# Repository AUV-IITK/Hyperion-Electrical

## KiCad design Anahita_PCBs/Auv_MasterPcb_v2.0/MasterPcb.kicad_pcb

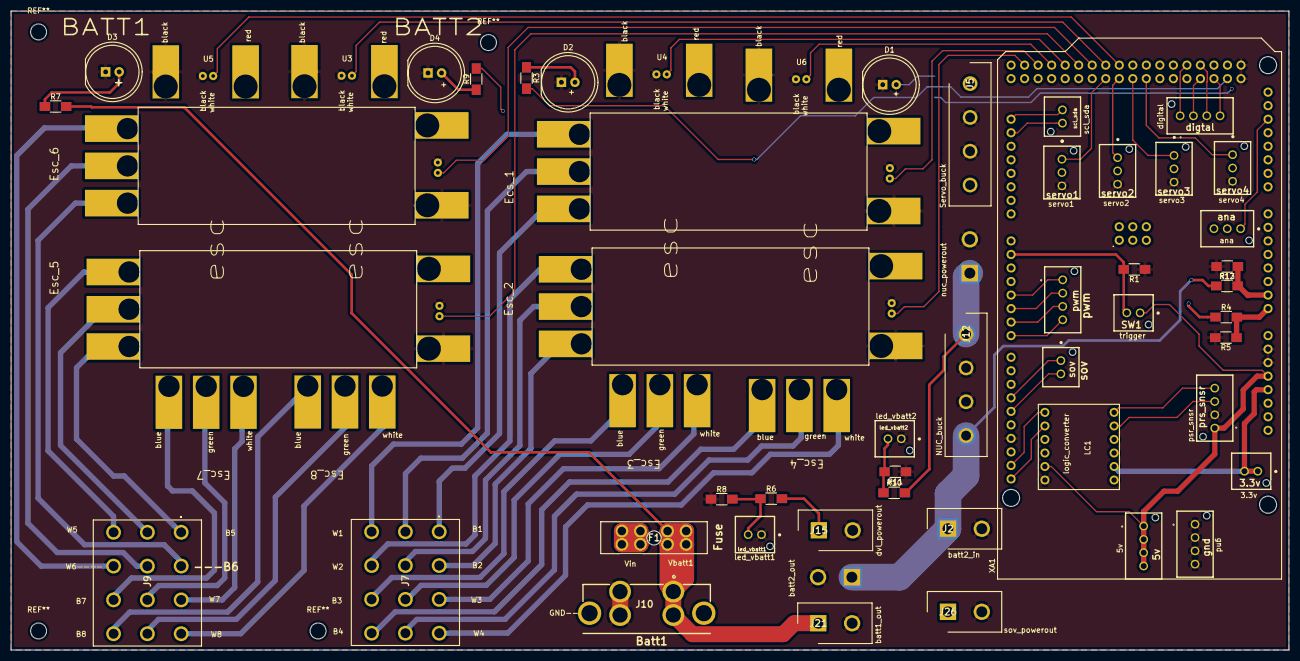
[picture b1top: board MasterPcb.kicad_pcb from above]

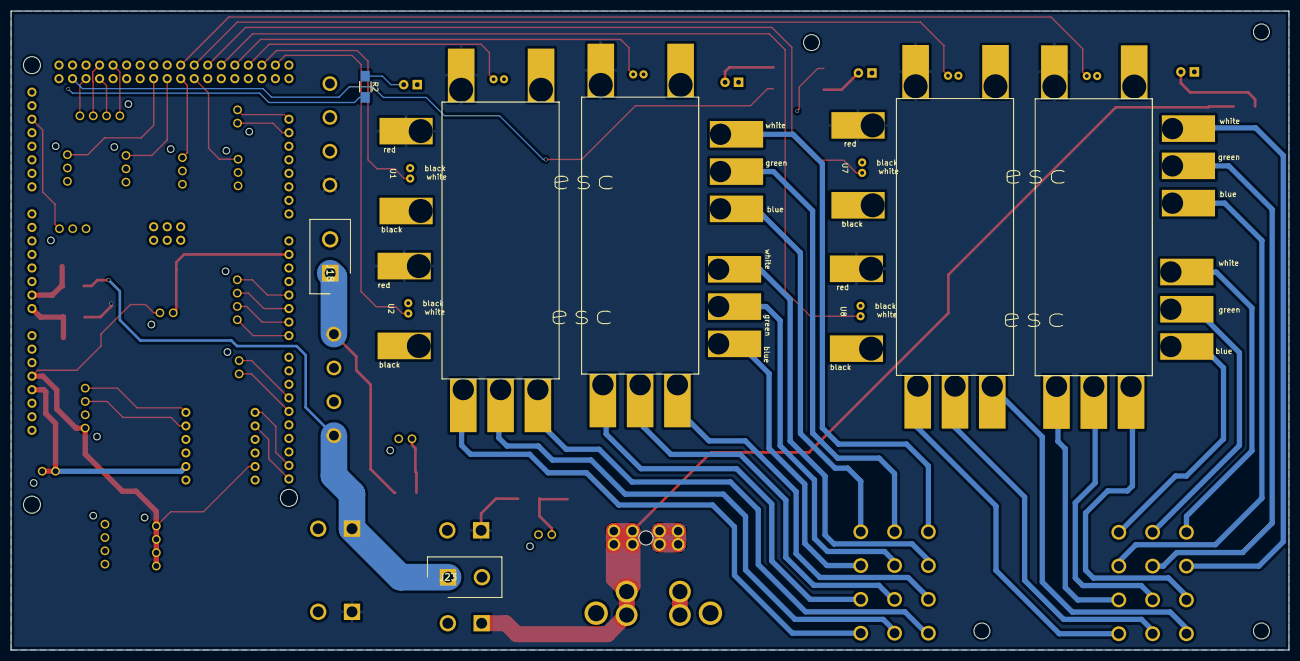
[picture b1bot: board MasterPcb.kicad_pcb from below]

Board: 4 copper layers, 240.0 x 120.0 mm, 55 parts (7 on the bottom side), 74 nets.

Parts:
3.3v: 3.3V_extras; 1x2_mini_lock
5v: 5V_extra; 1x4_mini_lock
D1, D2, D3, D4: LED; LED_D10.0mm
F1: Fuse
J2: nuc_battery; 1x2_Molex
J5: 5V_buck_servo; 1x4_Molex
J7: Thruster_1-4; 4_3connector
J9: Thruster_5-8; 4_3connector
J10: Thruster_power; power
J12: 19V_buck_nuc; 1x4_Molex
J15: dvl_power; 1x2_Molex
J18: Nuc_power; 1x2_Molex
J21: vbatt1_powerout; 1x2_Molex
J23: vbatt2_powerout; 1x2_Molex
J26: Sov_powerout; 1x2_Molex
LC1: Logic_Converter
R1, R2, R3, R5, R7, R9, R13: 1K; R_1206_HandSoldering
R4, R12: 24K; R_1206_HandSoldering
R6, R10: 1k; R_1206_HandSoldering
R8, R11: 4k; R_1206_HandSoldering
SW1: SW_DIP_x01; 1x2_mini_lock
U1, U2, U7, U8: ESCPINS; esc_redefined
U3, U4, U5, U6: ESCPINS; esc_mirror_redefined
XA1: Arduino_Mega2560_Shield
ana: Analog_Extras; 1x3_mini_lock
digtal: Dig_Extras; 1x4_mini_lock
gnd: GND_extras; 1x4_mini_lock
led_vbatt1: Led_vbatt1; 1x2_mini_lock
led_vbatt2: Led_vbatt2; 1x2_mini_lock
prs_snsr: Pressure_sensor_conn; 1x4_mini_lock
pwm: PWM_extras; 1x4_mini_lock
scl_sda: SDA_SCL_extras; 1x2_mini_lock
servo1: servo1; 1x3_mini_lock
servo2: servo2; 1x3_mini_lock
servo3: servo3; 1x3_mini_lock
servo4: servo4; 1x3_mini_lock
sov: Sov; 1x2_mini_lock

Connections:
/3.3V: 3.3v.1, 3.3v.2, LC1.8, XA1.3V3
/5V: 5v.1, 5v.2, 5v.3, 5v.4, LC1.2, SW1.1, XA1.5V1, prs_snsr.1
/5VBC: J5.1, servo1.2, servo2.2, servo3.2, servo4.2
/A0: R4.2, R5.1, XA1.A0
/A1: R12.2, R13.1, XA1.A1
/ANA1: XA1.A13, ana.1
/ANA2: XA1.A14, ana.2
/ANA3: XA1.A15, ana.3
/B1: J7.1, U1.1
/B2: J7.4, U2.1
/B3: J7.9, U4.3
/B4: J7.12, U6.3
/B5: J9.1, U8.1
/B6: J9.4, U7.1
/B7: J9.9, U5.3
/B8: J9.12, U3.3
/DIG1: XA1.D47, digtal.1
/DIG2: XA1.D48, digtal.2
/DIG3: XA1.D49, digtal.3
/DIG4: XA1.D50, digtal.4
/DVL: F1.5, F1.6, F1.7, F1.8, J5.4, J15.1, J26.1, R4.1, R6.2, U1.6, U2.6, U3.7, U4.7, U5.7, U6.7, U7.6, U8.6
/G1: J7.2, U1.2
/G2: J7.5, U2.2
/G3: J7.8, U4.2
/G4: J7.11, U6.2
/G5: J9.2, U8.2
/G6: J9.5, U7.2
/G7: J9.8, U5.2
/G8: J9.11, U3.2
/IN_1: XA1.D11, sov.1
/IN_2: XA1.D12, sov.2
/Led_vbatt1: R6.1, R8.2, led_vbatt1.2
/Led_vbatt2: R10.1, R11.2, led_vbatt2.2
/NUC: J12.1, J18.1, R10.2
/PWM-1: XA1.D4, pwm.1
/PWM-2: XA1.D5, pwm.2
/PWM-3: XA1.D6, pwm.3
/PWM-4: XA1.D7, pwm.4
/SCL1: XA1.D21, scl_sda.2
/SCL(HV): LC1.5, XA1.SCL
/SCL(PS): LC1.11, prs_snsr.3
/SDA1: XA1.D20, scl_sda.1
/SDA(HV): LC1.6, XA1.SDA
/SDA(PS): LC1.12, prs_snsr.4
/SER1: XA1.D34, servo1.1
/SER2: XA1.D36, servo2.1
/SER3: XA1.D38, servo3.1
/SER4: XA1.D40, servo4.1
/T-1: U1.4, XA1.D25
/T-2: U2.4, XA1.D23
/T-3: U4.4, XA1.D29
/T-4: U6.4, XA1.D27
/T-5: U8.4, XA1.D31
/T-6: U7.4, XA1.D33
/T-7: U5.4, XA1.D37
/T-8: U3.4, XA1.D35
/Test_led1: R3.2, XA1.D52
/Test_led2: R2.2, XA1.D53
/Trigger: R1.2, SW1.2, XA1.D1
/VBATT1: F1.1, F1.2, F1.3, F1.4, J10.1, J10.2, J21.1, R7.2
/VBATT2: J2.1, J12.4, J23.1, R9.2, R12.1
/W1: J7.3, U1.3
/W2: J7.6, U2.3
/W3: J7.7, U4.1
/W4: J7.10, U6.1
/W5: J9.3, U8.3
/W6: J9.6, U7.3
/W7: J9.7, U5.1
/W8: J9.10, U3.1
GND: D1.1, D2.1, D3.1, D4.1, J2.2, J5.2, J5.3, J10.3, J10.4, J12.2, J12.3, J15.2, J18.2, J21.2, J23.2, J26.2, LC1.1, R1.1, R5.2, R8.1, R11.1, R13.2, U1.5, U1.7, U2.5, U2.7, U3.5, U3.6, U4.5, U4.6, U5.5, U5.6, U6.5, U6.6, U7.5, U7.7, U8.5, U8.7, XA1.GND1, XA1.GND2, XA1.GND3, XA1.GND5, XA1.GND6, gnd.1, gnd.2, gnd.3, gnd.4, led_vbatt1.1, led_vbatt2.1, prs_snsr.2, servo1.3, servo2.3, servo3.3, servo4.3
unnamed: D1.2, R2.1
unnamed: D2.2, R3.1
unnamed: D3.2, R7.1
unnamed: D4.2, R9.1

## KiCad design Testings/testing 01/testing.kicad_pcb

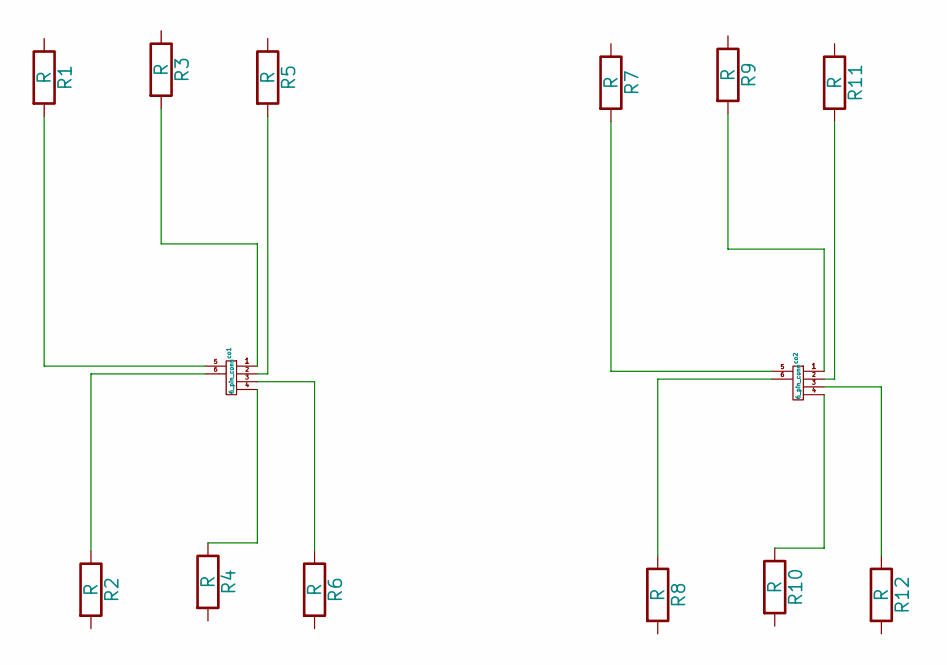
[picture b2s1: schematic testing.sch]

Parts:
R1, R2, R3, R4, R5, R6, R7, R8, R9, R10, R11, R12: R; R_1206
co1, co2: 6_pin_conn; edge card 0.65mm selfmade

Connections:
unnamed: R1.2, co1.5
unnamed: R2.1, co1.6
unnamed: R3.2, co1.1
unnamed: R4.1, co1.4
unnamed: R5.2, co1.2
unnamed: R6.1, co1.3
unnamed: R7.2, co2.5
unnamed: R8.1, co2.6
unnamed: R9.2, co2.1
unnamed: R10.1, co2.4
unnamed: R11.2, co2.2
unnamed: R12.1, co2.3

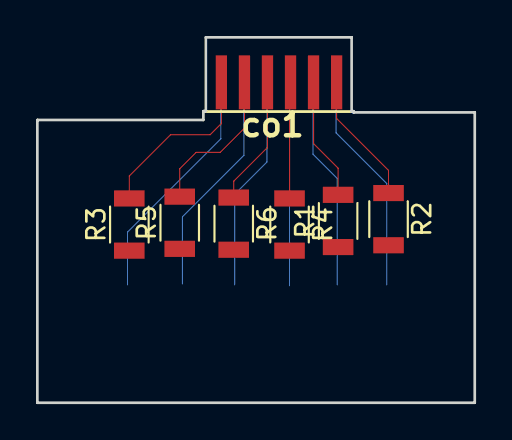
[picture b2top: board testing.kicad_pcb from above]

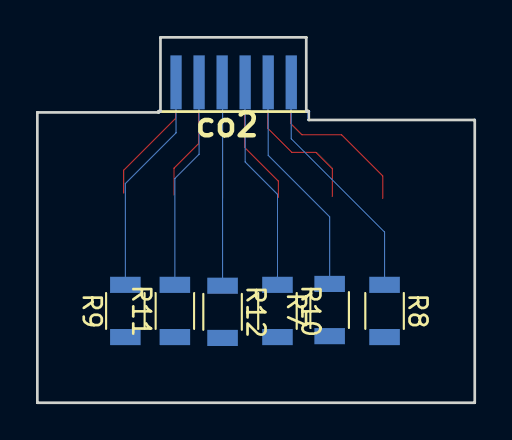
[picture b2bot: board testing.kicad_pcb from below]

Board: 2 copper layers, 24.3 x 20.3 mm, 14 parts (7 on the bottom side), 12 nets.

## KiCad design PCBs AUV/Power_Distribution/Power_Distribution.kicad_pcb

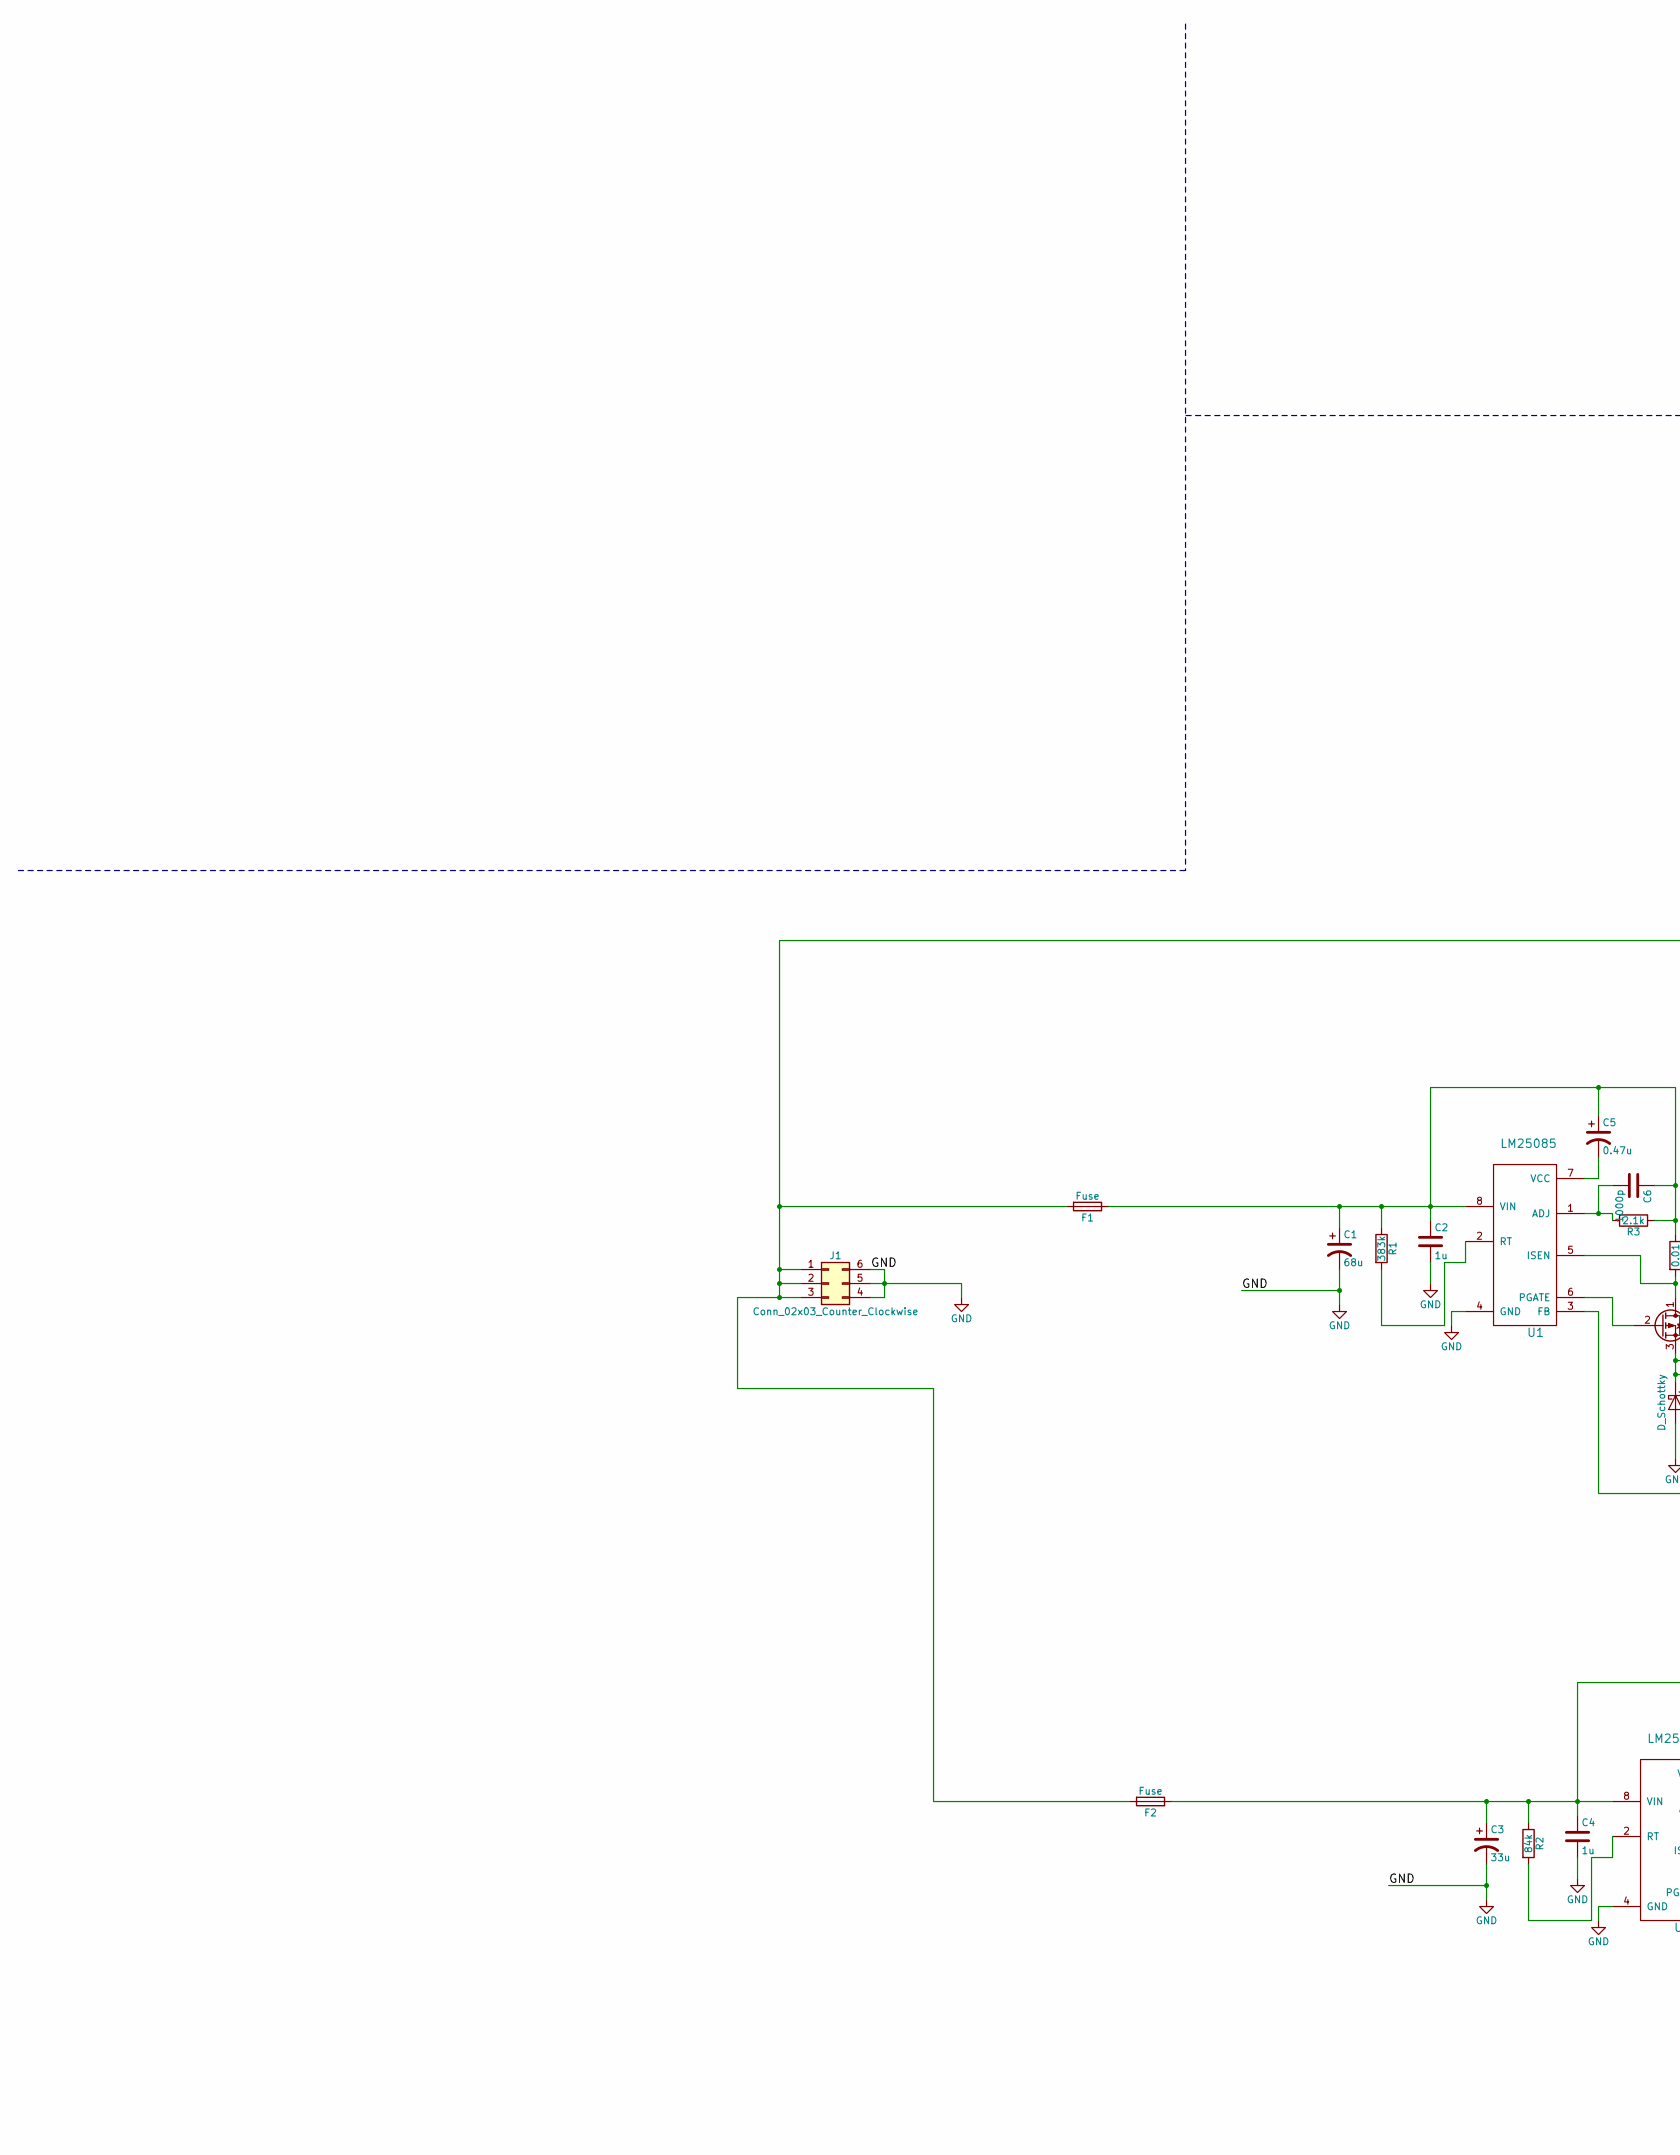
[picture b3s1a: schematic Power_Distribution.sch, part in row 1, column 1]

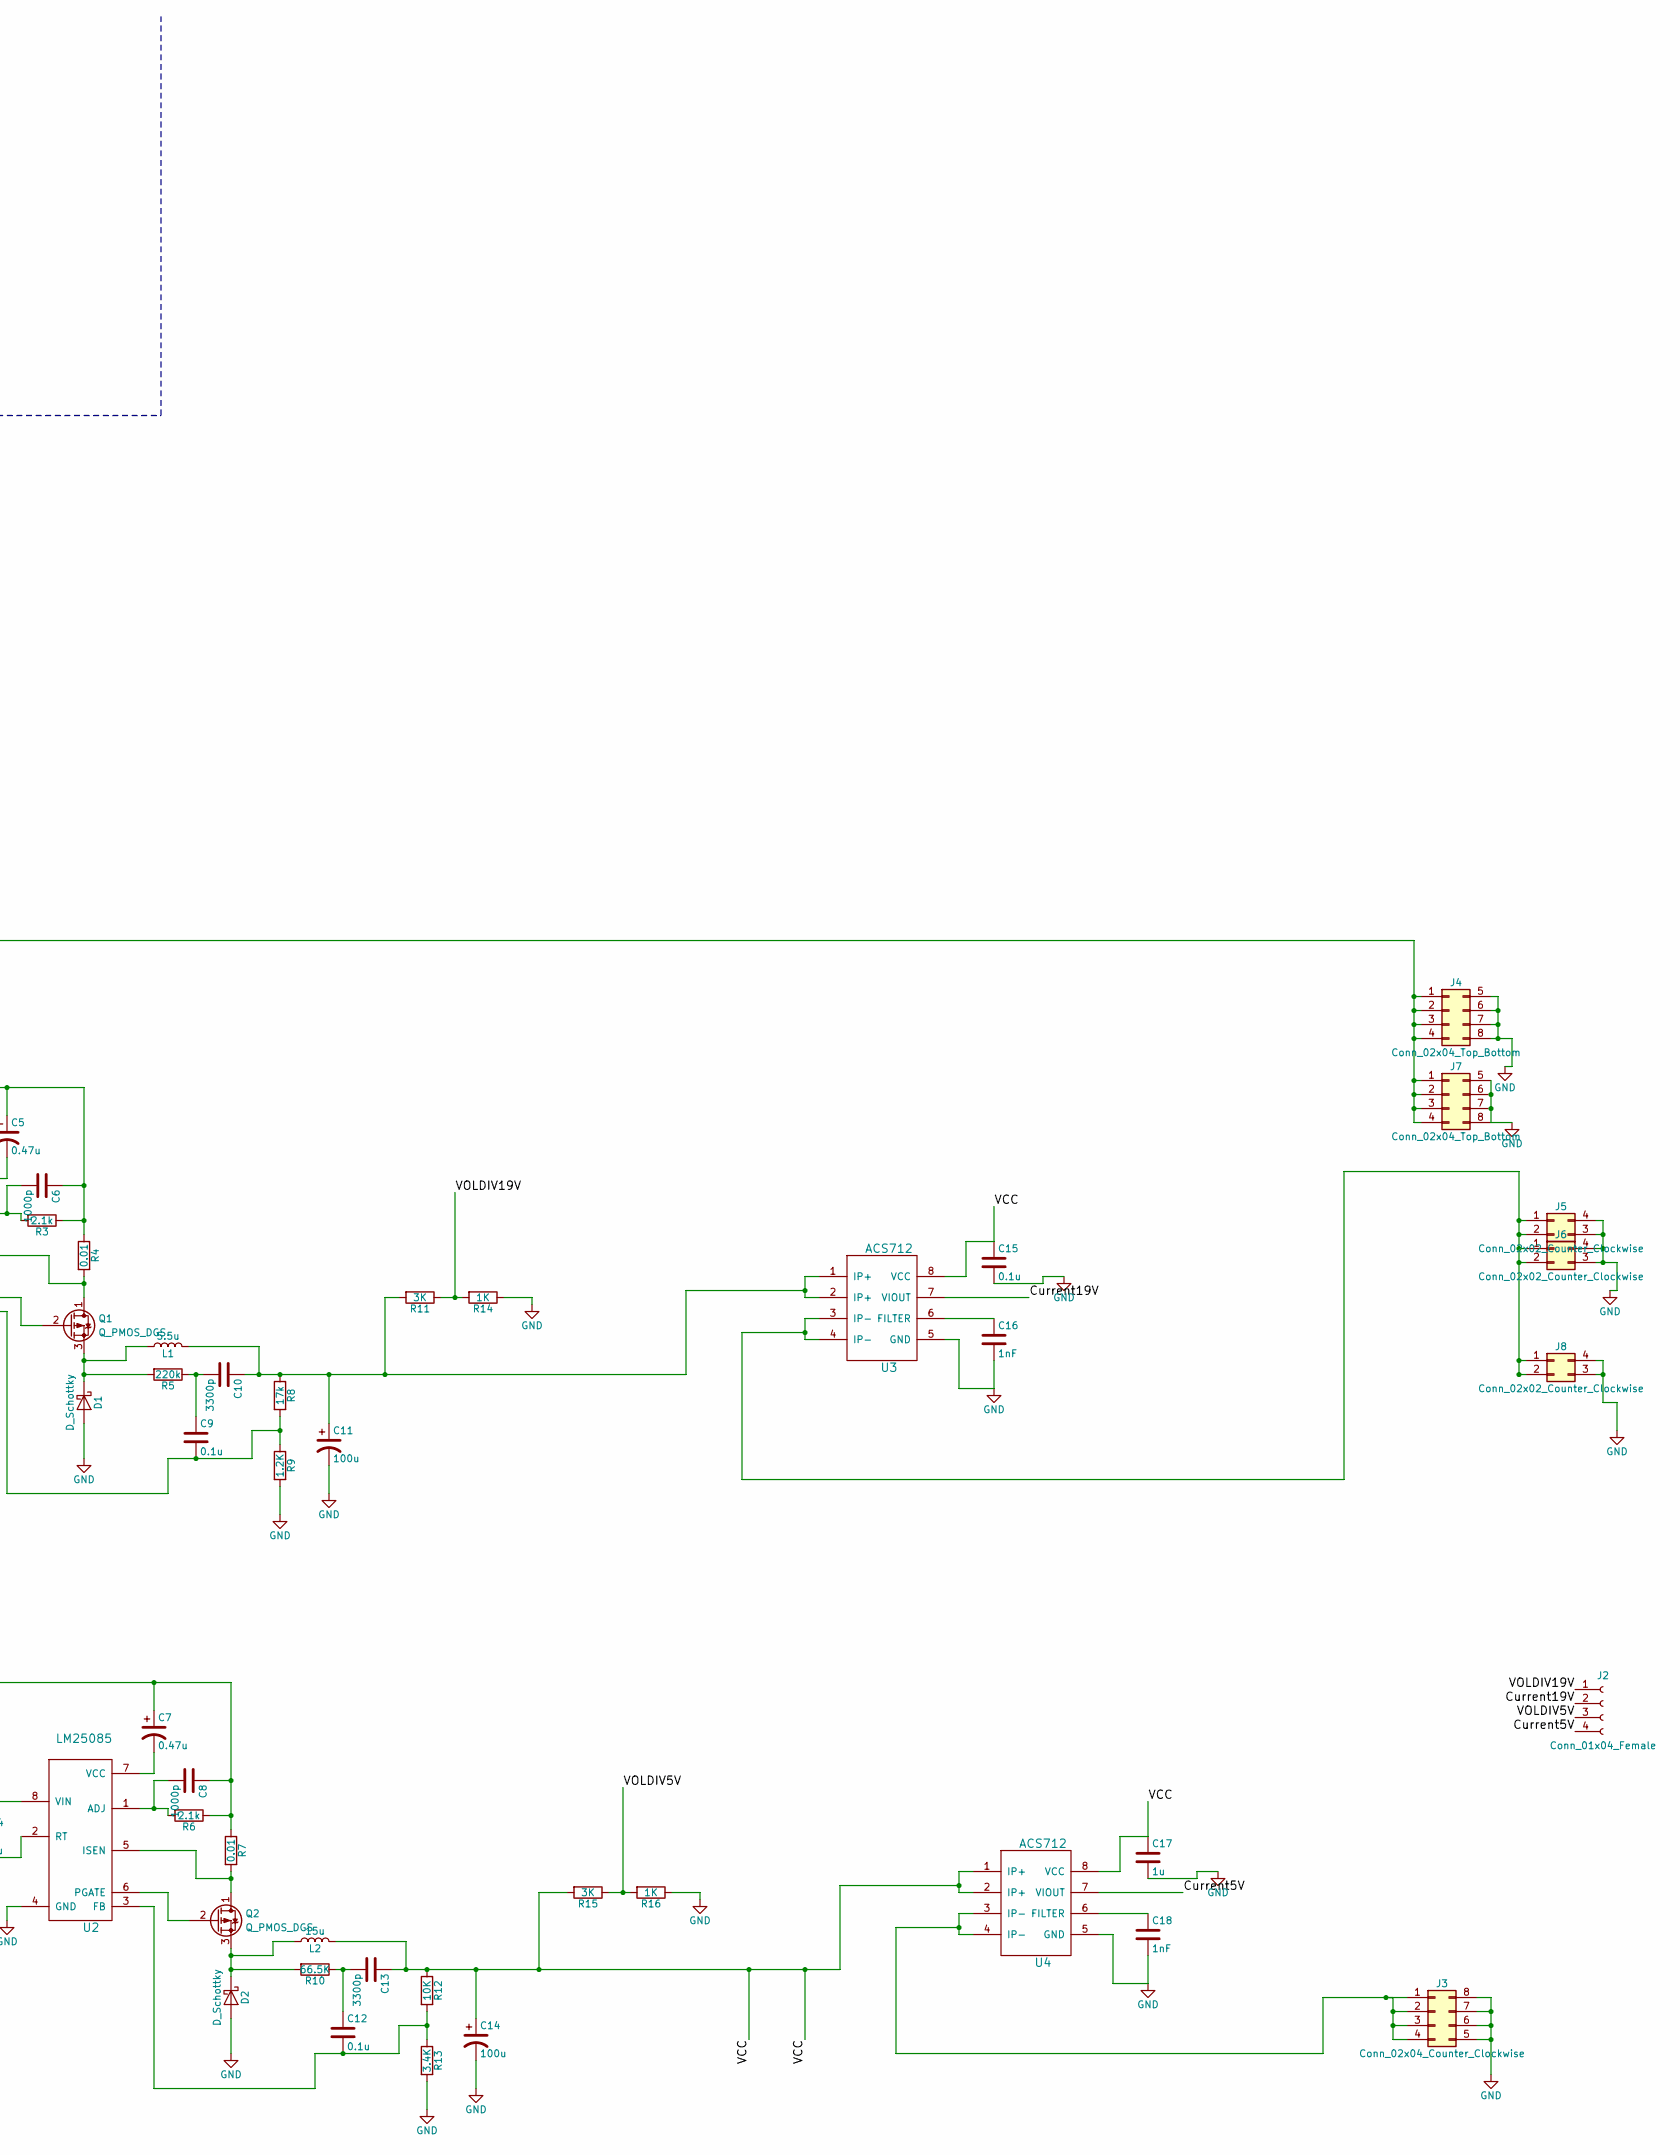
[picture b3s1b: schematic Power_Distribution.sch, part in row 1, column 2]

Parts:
C1: 68u; CP_Radial_D6.3mm_P2.50mm
C2, C4, C17: 1u; C_1206
C3: 33u; CP_Radial_D6.3mm_P2.50mm
C5, C7: 0.47u; CP_Radial_D5.0mm_P2.00mm
C6, C8: 1000p; C_1206
C9, C12, C15: 0.1u; C_1206
C10, C13: 3300p; C_1206
C11, C14: 100u; CP_Radial_D8.0mm_P3.50mm
C16, C18: 1nF; C_1206
D1, D2: D_Schottky; TO-220-2_Vertical
F1, F2: Fuse; Fuse_SMD1206_Wave
J1: Conn_02x03_Counter_Clockwise; Molex_MegaFit_2x03x5.70mm_Straight
J2: Conn_01x04_Female; Molex_PicoClasp_501331-0407_1x04_P1.0mm_Vertical
J3: Conn_02x04_Counter_Clockwise; Molex_MegaFit_2x04x5.70mm_Straight
J4, J7: Conn_02x04_Top_Bottom; Molex_MegaFit_2x04x5.70mm_Straight
J5, J6, J8: Conn_02x02_Counter_Clockwise; Molex_MegaFit_2x02x5.70mm_Straight
L1: 5.5u; L_10.4x10.4_H4.8
L2: 15u; inductor_13.5x12.5
Q1, Q2: Q_PMOS_DGS; TO-252-3_TabPin2
R1: 383k; R_1206
R2: 84k; R_1206
R3, R6: 2.1k; R_1206
R4, R7: 0.01; R_1206
R5: 220k; R_1206
R8: 17k; R_1206
R9: 1.2K; R_1206
R10: 66.5K; R_1206
R11, R15: 3K; R_1206
R12: 10K; R_1206
R13: 3.4K; R_1206
R14, R16: 1K; R_1206
U1, U2: LM25085; VSSOP-8_3.0x3.0mm_Pitch0.65mm
U3, U4: ACS712; SOIC-8_3.9x4.9mm_Pitch1.27mm

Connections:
/Current5V: J2.4, U4.7 (VIOUT)
/Current19V: J2.2, U3.7 (VIOUT)
/VCC: C13.1, C14.1, C15.1, C17.1, L2.2, R12.1, R15.2, U3.8 (VCC), U4.1 (IP+), U4.2 (IP+), U4.8 (VCC)
/VOLDIV5V: J2.3, R15.1, R16.2
/VOLDIV19V: J2.1, R11.1, R14.2
GND: C1.2, C2.2, C3.2, C4.2, C11.2, C14.2, C15.2, C16.2, C17.2, C18.2, D1.2 (A), D2.2 (A), J1.4, J1.5, J1.6, J3.5, J3.6, J3.7, J3.8, J4.5, J4.6, J4.7, J4.8, J5.3, J5.4, J6.3, J6.4, J7.5, J7.6, J7.7, J7.8, J8.3, J8.4, R9.2, R13.2, R14.1, R16.1, U1.4 (GND), U2.4 (GND), U3.5 (GND), U4.5 (GND)
unnamed: C1.1, C2.1, C5.1, C6.1, F1.1, R1.1, R3.1, R4.1, U1.8 (VIN)
unnamed: C3.1, C4.1, C7.1, C8.1, F2.1, R2.1, R6.1, R7.1, U2.8 (VIN)
unnamed: C5.2, U1.7 (VCC)
unnamed: C6.2, R3.2, U1.1 (ADJ)
unnamed: C7.2, U2.7 (VCC)
unnamed: C8.2, R6.2, U2.1 (ADJ)
unnamed: C9.2, R8.2, R9.1, U1.3 (FB)
unnamed: C10.1, C11.1, L1.2, R8.1, R11.2, U3.1 (IP+), U3.2 (IP+)
unnamed: C9.1, C10.2, R5.1
unnamed: C12.1, C13.2, R10.1
unnamed: C12.2, R12.2, R13.1, U2.3 (FB)
unnamed: C16.1, U3.6 (FILTER)
unnamed: C18.1, U4.6 (FILTER)
unnamed: D1.1 (K), L1.1, Q1.3 (S), R5.2
unnamed: D2.1 (K), L2.1, Q2.3 (S), R10.2
unnamed: F1.2, F2.2, J1.1, J1.2, J1.3, J4.1, J4.2, J4.3, J4.4, J7.1, J7.2, J7.3, J7.4
unnamed: J3.1, J3.2, J3.3, J3.4, U4.3 (IP-), U4.4 (IP-)
unnamed: J5.1, J5.2, J6.1, J6.2, J8.1, J8.2, U3.3 (IP-), U3.4 (IP-)
unnamed: Q1.1 (D), R4.2, U1.5 (ISEN)
unnamed: Q1.2 (G), U1.6 (PGATE)
unnamed: Q2.1 (D), R7.2, U2.5 (ISEN)
unnamed: Q2.2 (G), U2.6 (PGATE)
unnamed: R1.2, U1.2 (RT)
unnamed: R2.2, U2.2 (RT)

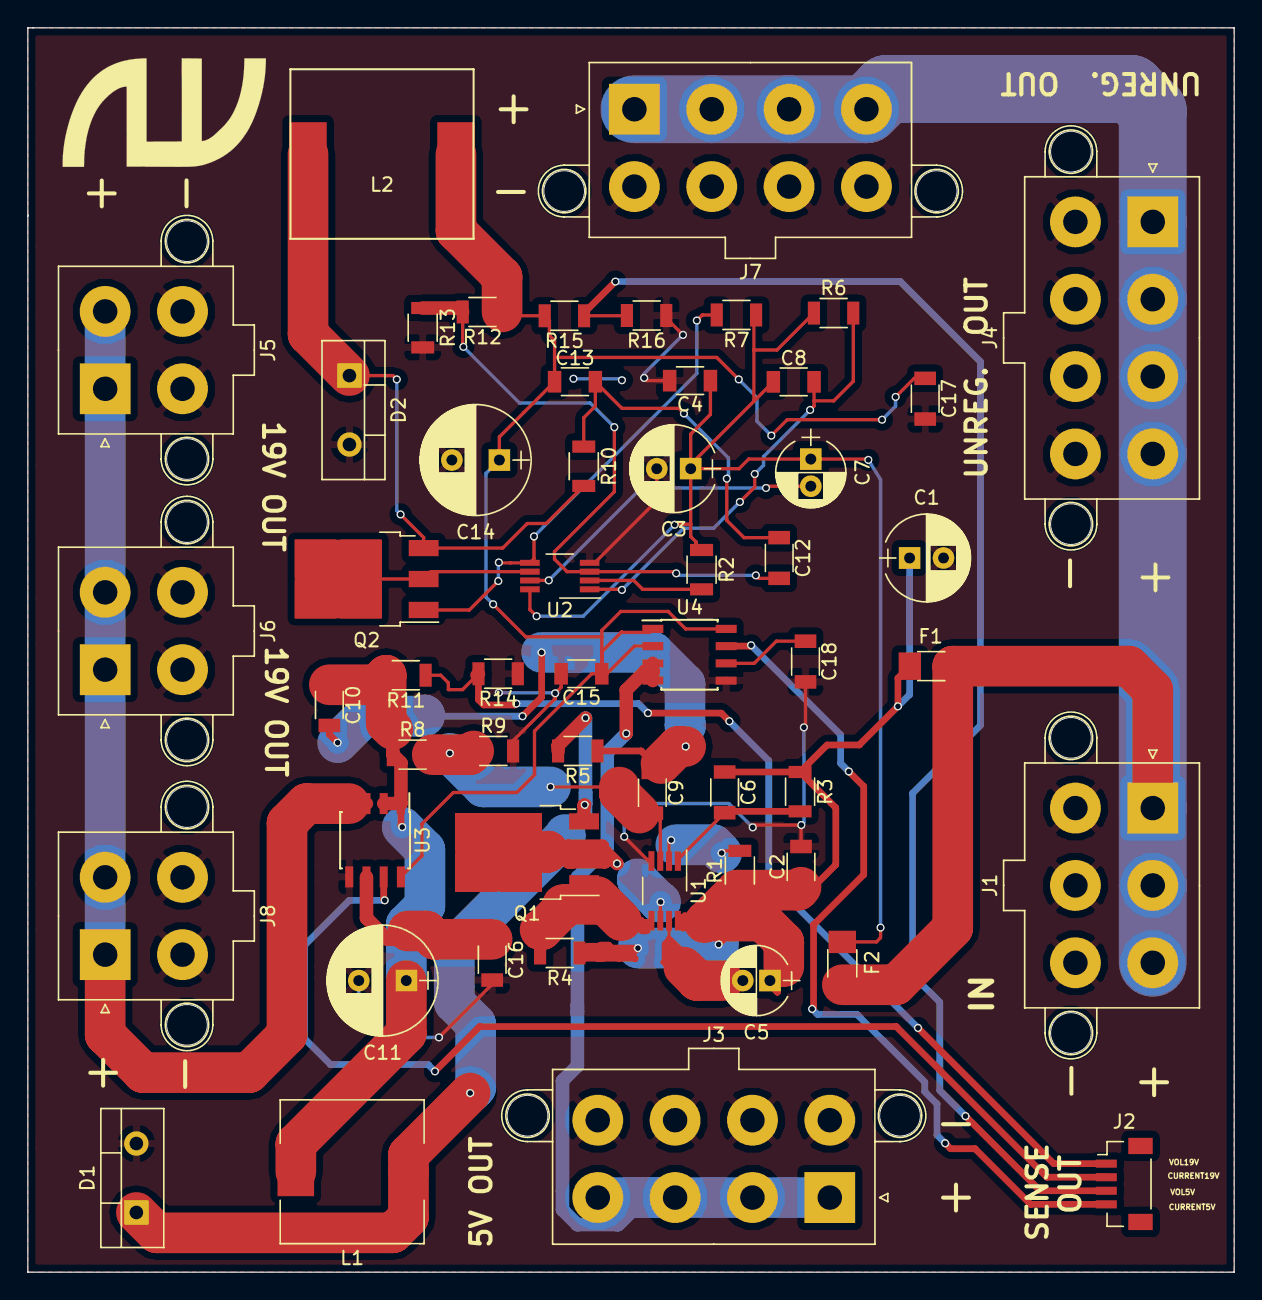
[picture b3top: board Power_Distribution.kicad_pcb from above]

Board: 2 copper layers, 88.9 x 91.7 mm, 54 parts (0 on the bottom side), 30 nets.

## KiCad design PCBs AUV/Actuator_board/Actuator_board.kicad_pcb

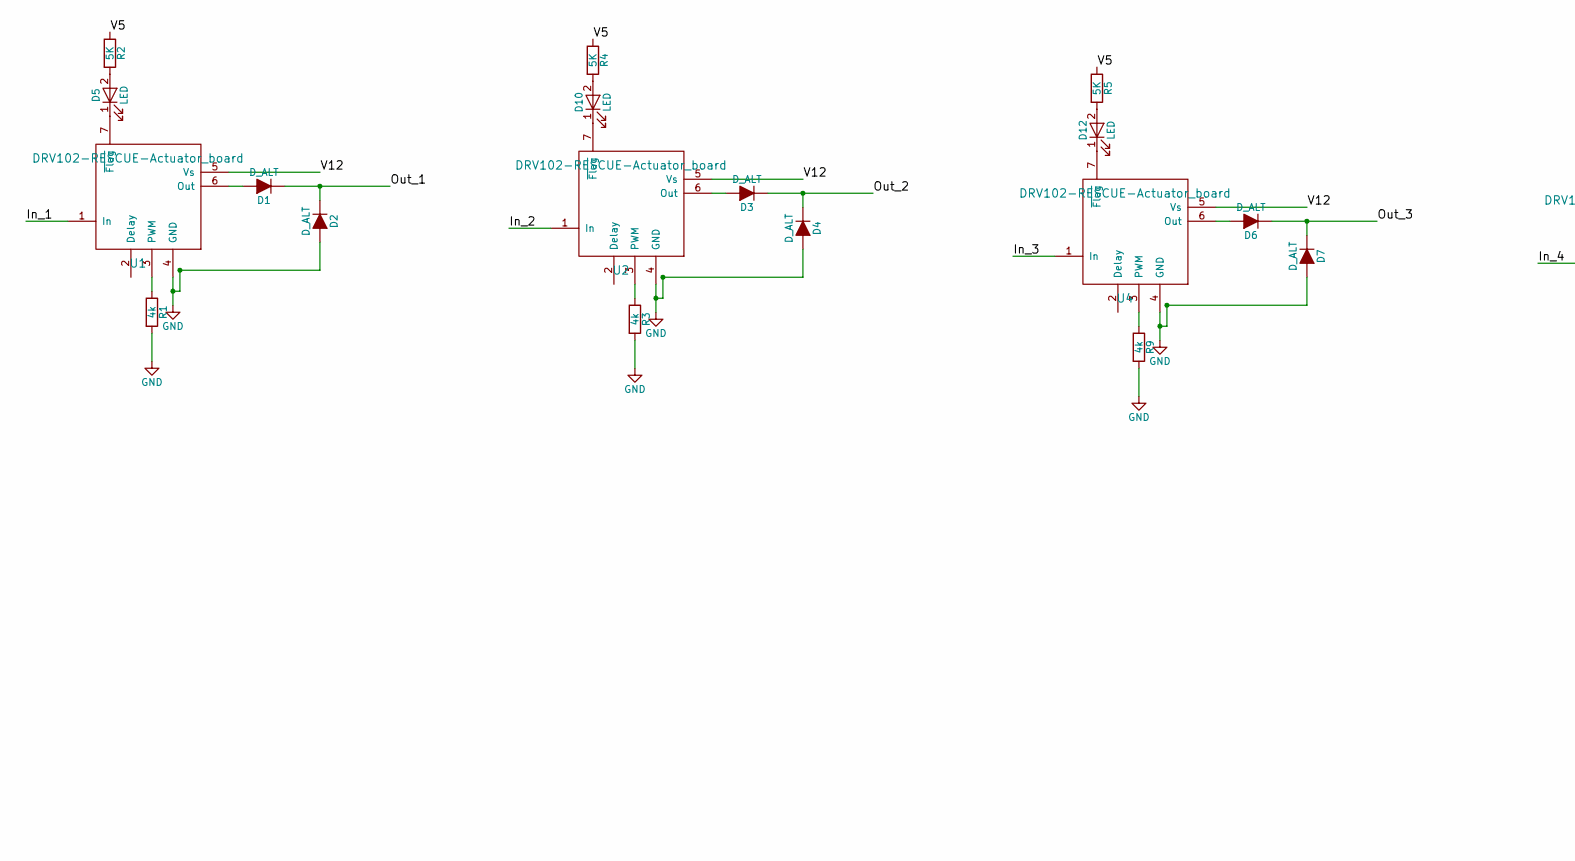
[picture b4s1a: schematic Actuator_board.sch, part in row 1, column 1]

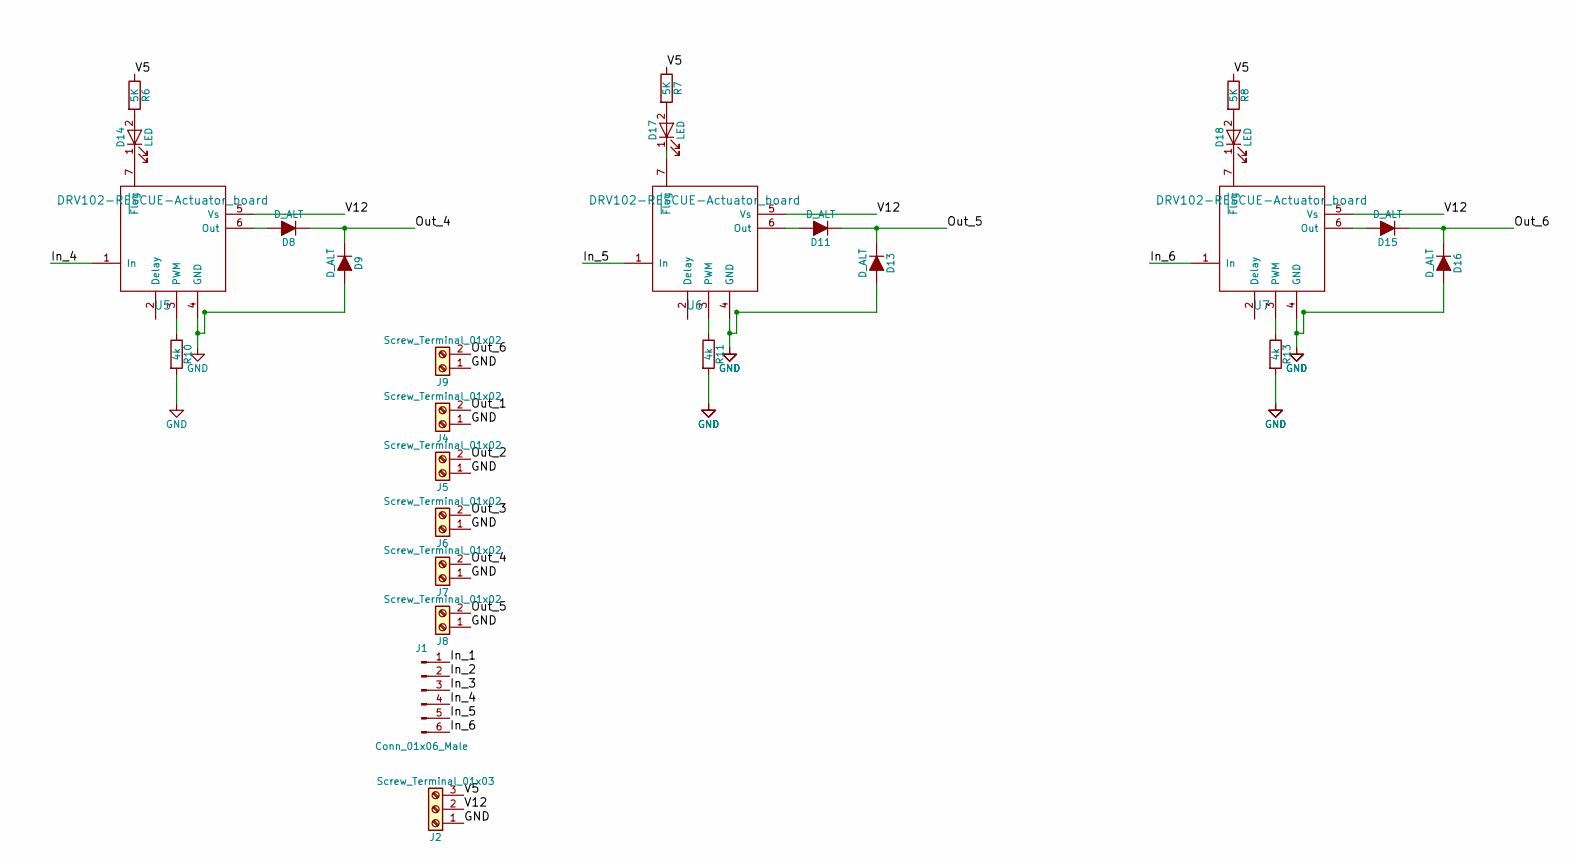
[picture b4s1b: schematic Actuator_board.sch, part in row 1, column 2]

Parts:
D1, D2, D3, D4, D6, D7, D8, D9, D11, D13, D15, D16: D_ALT; DO-214AB
D5: LED; LED_D2.0mm_W4.8mm_H2.5mm_FlatTop
D10, D12, D14, D17, D18: LED; LED_D3.0mm
J1: Conn_01x06_Male; Pin_Header_Straight_1x06_Pitch2.54mm
J2: Screw_Terminal_01x03; TerminalBlock_bornier-3_P5.08mm
J4, J5, J6, J7, J8, J9: Screw_Terminal_01x02; TerminalBlock_bornier-2_P5.08mm
R1, R3, R9, R10, R11, R13: 4k; R_1206
R2, R4, R5, R6, R7, R8: 5K; R_1206
U1, U2, U4, U5, U6, U7: DRV102-RESCUE-Actuator_board; TO-263-7_TabPin4

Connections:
/In_1: J1.1, U1.1 (In)
/In_2: J1.2, U2.1 (In)
/In_3: J1.3, U4.1 (In)
/In_4: J1.4, U5.1 (In)
/In_5: J1.5, U6.1 (In)
/In_6: J1.6, U7.1 (In)
/Out_1: D1.1 (K), D2.1 (K), J4.2
/Out_2: D3.1 (K), D4.1 (K), J5.2
/Out_3: D6.1 (K), D7.1 (K), J6.2
/Out_4: D8.1 (K), D9.1 (K), J7.2
/Out_5: D11.1 (K), D13.1 (K), J8.2
/Out_6: D15.1 (K), D16.1 (K), J9.2
/V5: J2.3, R2.1, R4.1, R5.1, R6.1, R7.1, R8.1
/V12: J2.2, U1.5 (Vs), U2.5 (Vs), U4.5 (Vs), U5.5 (Vs), U6.5 (Vs), U7.5 (Vs)
GND: D2.2 (A), D4.2 (A), D7.2 (A), D9.2 (A), D13.2 (A), D16.2 (A), J2.1, J4.1, J5.1, J6.1, J7.1, J8.1, J9.1, R1.2, R3.2, R9.2, R10.2, R11.2, R13.2, U1.4 (GND), U2.4 (GND), U4.4 (GND), U5.4 (GND), U6.4 (GND), U7.4 (GND)
unnamed: D1.2 (A), U1.6 (Out)
unnamed: D3.2 (A), U2.6 (Out)
unnamed: D5.1 (K), U1.7 (~Flag)
unnamed: D5.2 (A), R2.2
unnamed: D6.2 (A), U4.6 (Out)
unnamed: D8.2 (A), U5.6 (Out)
unnamed: D10.1 (K), U2.7 (~Flag)
unnamed: D10.2 (A), R4.2
unnamed: D11.2 (A), U6.6 (Out)
unnamed: D12.1 (K), U4.7 (~Flag)
unnamed: D12.2 (A), R5.2
unnamed: D14.1 (K), U5.7 (~Flag)
unnamed: D14.2 (A), R6.2
unnamed: D15.2 (A), U7.6 (Out)
unnamed: D17.1 (K), U6.7 (~Flag)
unnamed: D17.2 (A), R7.2
unnamed: D18.1 (K), U7.7 (~Flag)
unnamed: D18.2 (A), R8.2
unnamed: R1.1, U1.3 (PWM)
unnamed: R3.1, U2.3 (PWM)
unnamed: R9.1, U4.3 (PWM)
unnamed: R10.1, U5.3 (PWM)
unnamed: R11.1, U6.3 (PWM)
unnamed: R13.1, U7.3 (PWM)

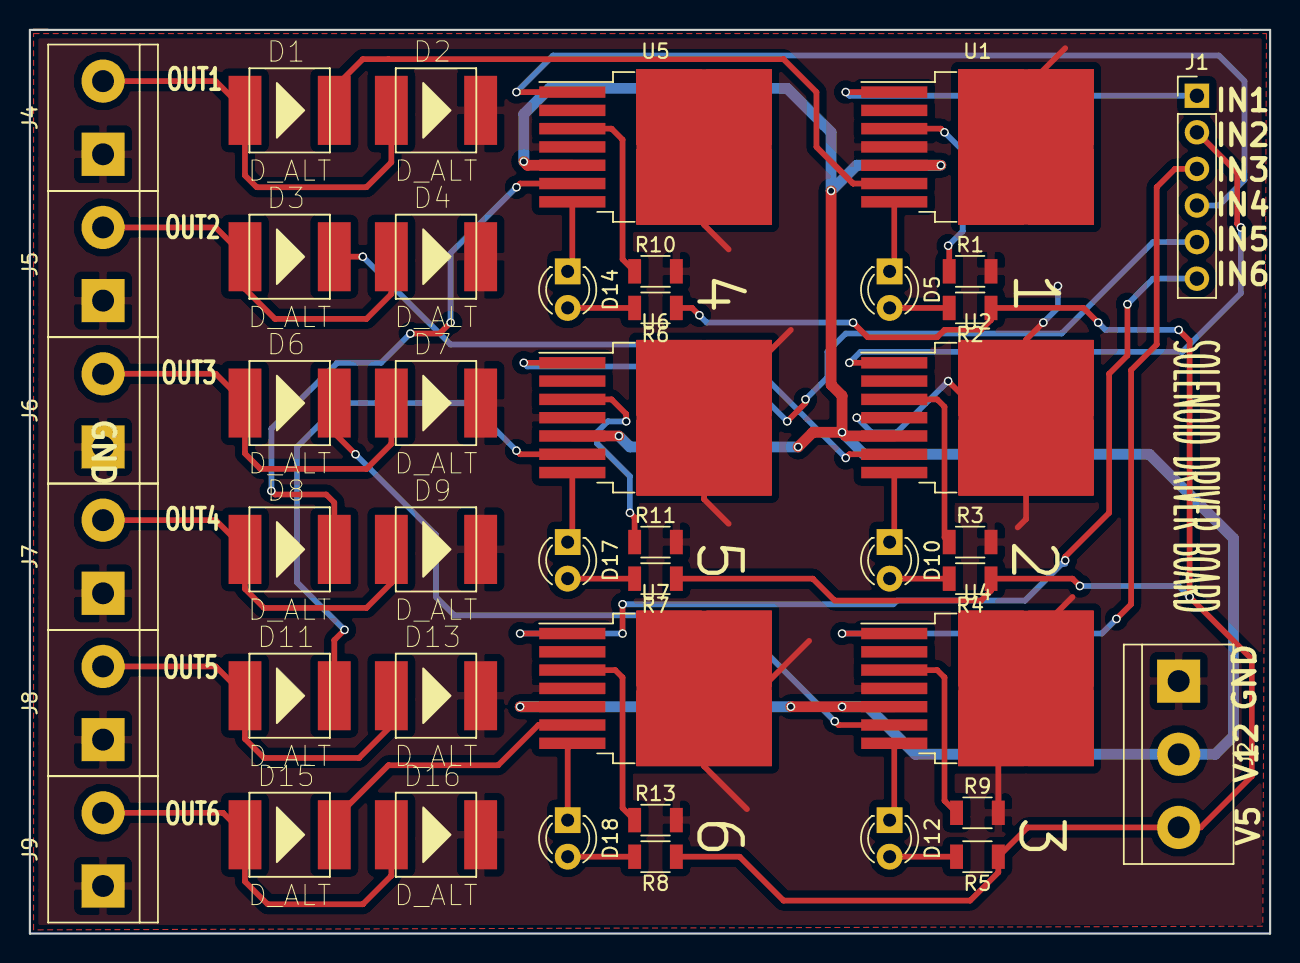
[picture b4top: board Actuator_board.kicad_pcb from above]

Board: 2 copper layers, 86.1 x 62.7 mm, 44 parts (0 on the bottom side), 39 nets.
